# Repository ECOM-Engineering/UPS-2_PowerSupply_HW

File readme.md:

# UPS-2 Power Supply Hardware

***This read me is currently under development***  

This project is the hardware part of the superior **UPS-2** project  
https://github.com/ECOM-Engineering/UPS-2_Uninteruptible-Power-Supply.git .

If you are looking for a simple power-down switch, please refer to the  **s_shut** project  
https://github.com/ECOM-Engineering/Raspberry-Shutdown.git .

## Hardware description

### Summary

**Please refer to the [UPS-2 schematic](./doc/UPS-2 Schematic.pdf).**

UPS-2 hardware builds an uniterruptible, efficient  power supply with a wide input range. There are no glitches during switching and very low power dissipation resulting in cool operation.

Switching between main supply and backup source (usually a battery) is performed by the dedicated [TPS2121](https://www.ti.com/product/TPS2121) switch by TI with no CPU intervention. This guaranties a seamless switchover between the two power inputs. Furthermore, this design allows high efficiency thanks to the very low 56mΩ on resistance. 

5V output voltage regulation is performed by the TI [TPS56339](https://www.ti.com/product/TPS56339) 3A buck converter with an efficieny of >94%. 

Output is protected by the Raspberry standard 'ideal diode' against back driving, if Rasbperry Pi is powered through it's USB connector.

### Input Selector and Power Supply

Please refer to the [TPS2121 data sheet](https://www.ti.com/lit/ds/symlink/tps2121.pdf?ts=1623582270012&ref_url=https%253A%252F%252Fwww.google.com%252F) 

TPS2121 (U2) Power Mux is operated in th 'fast switchover' mode: If input PR1 (derived from Main input) falls below approx. 8V,  U2 switches over to the Battery input without CPU intervention. Capacitors C5, C6, C7 remove switching spikes and Voltage drop during switching over. C7 is a low EMC type with enough capacity in order to limit voltage drop during switching at up to 3A output load.

Voltage scaler allows measuring supply voltages by the ADC of the CPU. In order to minimize quiet current of the voltage sources, it uses as high resistors as possible regarding the input bias of the ADC.

### System Controller

System Controller provides 

- communication with the user via LED indicators and a switch for manual controlling 
- communication with the Raspberry CPU via serial or parallel interface
- firmware flash update via debug port or via Raspberry serial interface

UPS-2 uses an Cortex M0+ CPU of the [STM32G030](https://www.st.com/en/microcontrollers-microprocessors/stm32g030j6.html)  from STMicroelectronics. This CPU provides an incredible 32Bit performance/price ratio. 

### Debug Connector

Debug connetor J6 uses the SWD serial wire debug and flash programming. Pins 1..4 are compatible with the STM32 eval and diccovery boards.

### Hat EEPROM

This memory meets the [Raspberry-Pi Hat specification](https://github.com/raspberrypi/hats) and can be programmed by the user. **Currently, this EEPROM is not used and is unprogrammed.**

### Mode selection

For Jumper Settings and functions please refer to the [UPS-2_User Guide](../UPS-2-Project-repository/UPS-2_Uninteruptible-Power-Supply/doc/user-guide.md)

###  PCB

Board outline corresponds to the mechanical Raspberry-Pi Hat specification.   
UPS-2 uses a 1.6mm 2-layer PCB.

## Used Tools

- [KiCad](https://kicad.org/) EDA system for schematic an PCB layout.
- [Typora](https://typora.io/) for markdown texts (this readme)
- [Libre Office](https://www.libreoffice.org/) for Text and illustrations
- [git](https://git-scm.com/) and [github](https://github.com/)

## Production

This project contains all documents necessary for production including BOM with digikey part numbers and Gerber files for PCB 2-layer production.

In order to make production as simple as possible, PCB uses mostly SMD components that may be produced and soldered by nearly any prototyping service (no fine pitch, 0805 resistors, capacitors). First prototypes have been produced in Switzerland by https://www.quick-pick.ch/. 

## License

**Hardware is licensed under the open source license**  [**CERN-OHLW v2**](https://github.com/ECOM-Engineering/UPS-2_PowerSupply_HW/blob/main/doc/cern_ohl_w_v2.pdf) .

Document Copyright (c) 2021 Klaus Mezger, open source under MIT license.

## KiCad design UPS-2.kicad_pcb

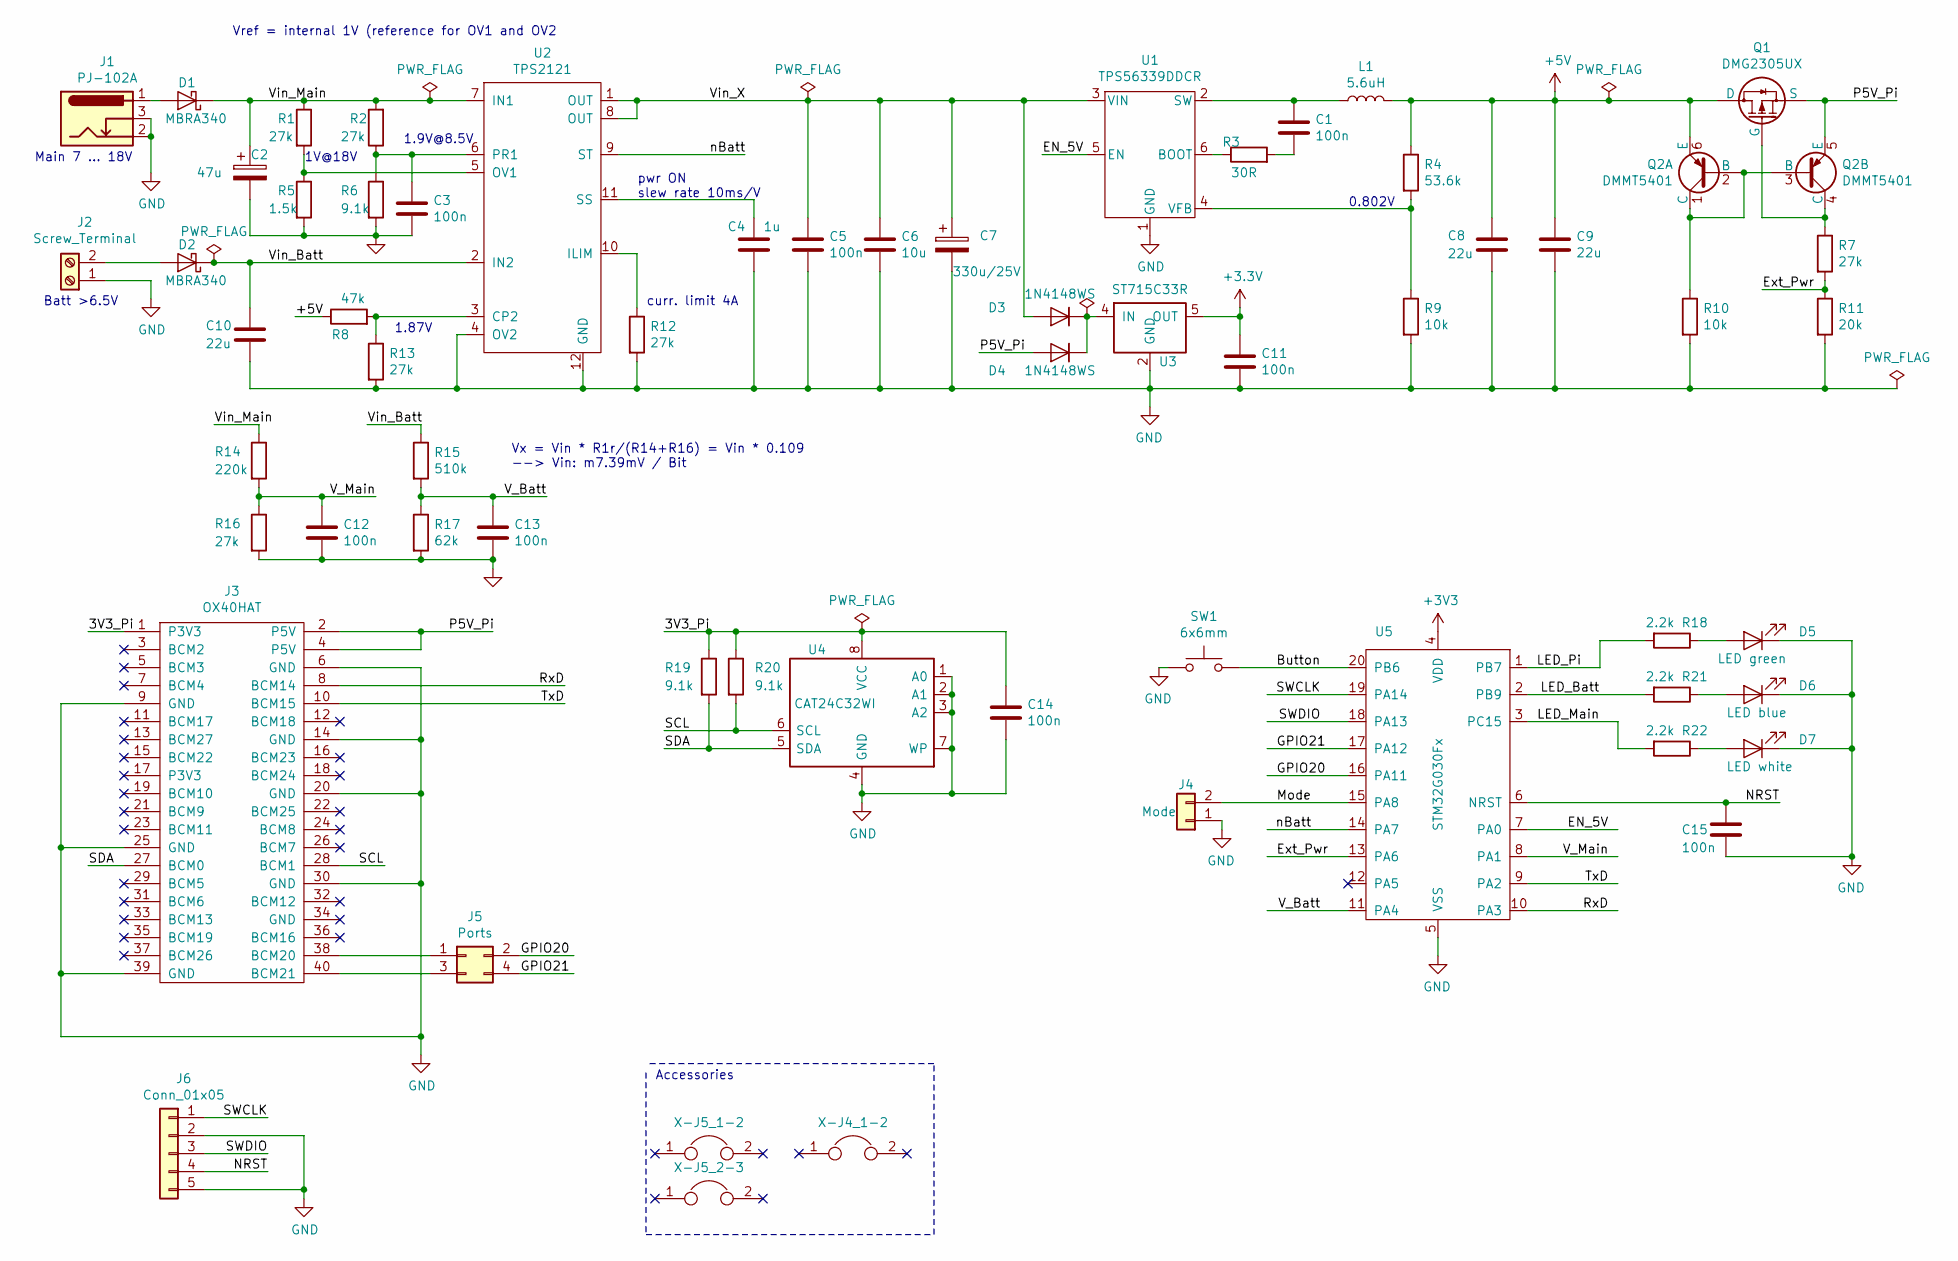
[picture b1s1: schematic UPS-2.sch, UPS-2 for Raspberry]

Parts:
C1, C3, C11, C12, C13, C14, C15: 100n; C_0805_2012Metric
C2: 47u; CP_Elec_6.3x5.3; Digi-Key_PN PCE3908CT-ND
C4: 1u; C_0805_2012Metric; Digi-Key_PN 399-7410-1-ND
C5: 100n; C_0805_2012Metric; Digi-Key_PN 399-1169-1-ND
C6: 10u; C_0805_2012Metric; Digi-Key_PN 445-9015-1-ND
C7: 330u/25V; CP_Elec_8x11.9; Digi-Key_PN PCE3906CT-ND
C8, C9: 22u; C_0805_2012Metric; Digi-Key_PN 445-14560-1-ND
C10: 22u; C_0805_2012Metric
D1, D2: MBRA340; D_SMA; Digi-Key_PN MBRA340T3GOSCT-ND
D3, D4: 1N4148WS; D_SOD-323; Digi-Key_PN 1N4148WSTR
D5: LED green; LED_1206_3216Metric; Digi-Key_PN 1516-1073-1-ND
D6: LED blue; LED_1206_3216Metric; Digi-Key_PN 1516-1072-1-ND
D7: LED white; LED_1206_3216Metric; Digi-Key_PN 1516-1074-1-ND
J1: PJ-102A; BarrelJack_CUI_PJ-102AH_Horizontal; Digi-Key_PN CP-102A-ND
J2: Screw_Terminal; TerminalBlock_bornier-2_P5.08mm; Digi-Key_PN ED2609-ND
J3: OX40HAT; PinSocket_2x20_P2.54mm_Vertical; Digi-Key_PN 612-HLE-120-02-F-DV-BE-ND
J4: Mode; PinHeader_1x02_P2.54mm_Vertical
J5: Ports; PinHeader_2x02_P2.54mm_Vertical
J6: Conn_01x05; PinHeader_1x05_P2.54mm_Vertical
L1: 5.6uH; L_Bourns_SRR1260; Digi-Key_PN SRR1260A-5R6YCT-ND
Q1: DMG2305UX; SOT-23; Digi-Key_PN DMG2305UX-13DICT-ND
Q2: DMMT5401; SOT-23-6; Digi-Key_PN DMMT5401-FDICT-ND
R1, R2, R7, R12, R13, R16: 27k; R_0805_2012Metric
R3: 30R; R_0805_2012Metric
R4: 53.6k; R_0805_2012Metric
R5: 1.5k; R_0805_2012Metric
R6, R19, R20: 9.1k; R_0805_2012Metric
R8: 47k; R_0805_2012Metric
R9, R10: 10k; R_0805_2012Metric
R11: 20k; R_0805_2012Metric
R14: 220k; R_0805_2012Metric
R15: 510k; R_0805_2012Metric
R17: 62k; R_0805_2012Metric
R18, R21, R22: 2.2k; R_0805_2012Metric
SW1: 6x6mm; SW_SPST_PTS645; Digi-Key_PN CKN9087DKR-ND
U1: TPS56339DDCR; SOT-23-6; Digi-Key_PN 296-53568-1-ND
U2: TPS2121; TPS2121RUXR_V2; Digi-Key_PN 296-53410-1-ND
U3: ST715C33R; SOT-353_SC-70-5; Digi-Key_PN 497-15509-1-ND
U4: CAT24C32WI; SO-8_3.9x4.9mm_P1.27mm; Digi-Key_PN CAT24C32WI-GT3CT-ND
U5: STM32G030Fx; TSSOP-20_4.4x6.5mm_P0.65mm; Digi-Key_PN STM32G030F6P6
X-J4_1-2, X-J5_1-2, X-J5_2-3: Jumper 2.54; Digi-Key_PN S9337-ND

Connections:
+5V: C8.1, C9.1, L1.2, Q1.3 (D), Q2.6 (E), R4.1, R8.1
/3V3_Pi: C14.1, J3.1 (P3V3), R19.1, R20.1, U4.8 (VCC)
/Button: SW1.1, U5.20 (PB6)
/EN_5V: U1.5 (EN), U5.7 (PA0)
/Ext_Pwr: R7.2, R11.1, U5.13 (PA6)
/GPIO20: J5.2, U5.16 (PA11)
/GPIO21: J5.4, U5.17 (PA12)
/LED_Batt: R21.2, U5.2 (PB9)
/LED_Main: R22.2, U5.3 (PC15)
/LED_Pi: R18.2, U5.1 (PB7)
/Mode: J4.2, U5.15 (PA8)
/NRST: C15.1, J6.4, U5.6 (NRST)
/P5V_Pi: D4.2 (A), J3.2 (P5V), J3.4 (P5V), Q1.2 (S), Q2.5 (E)
/RxD: J3.8 (BCM14), U5.10 (PA3)
/SCL: J3.28 (BCM1), R20.2, U4.6 (SCL)
/SDA: J3.27 (BCM0), R19.2, U4.5 (SDA)
/SWCLK: J6.1, U5.19 (PA14)
/SWDIO: J6.3, U5.18 (PA13)
/TxD: J3.10 (BCM15), U5.9 (PA2)
/V_Batt: C13.1, R15.2, R17.1, U5.11 (PA4)
/V_Main: C12.1, R14.2, R16.1, U5.8 (PA1)
/Vin_Batt: C10.1, D2.1 (K), R15.1, U2.2 (IN2)
/Vin_Main: C2.1, D1.1 (K), R1.1, R2.2, R14.1, U2.7 (IN1)
/Vin_X: C5.1, C6.1, C7.1, D3.2 (A), U1.3 (VIN), U2.1 (OUT), U2.8 (OUT)
/nBatt: U2.9 (ST), U5.14 (PA7)
GND: C2.2, C3.2, C4.2, C5.2, C6.2, C7.2, C8.2, C9.2, C10.2, C11.2, C12.2, C13.2, C14.2, C15.2, D5.1 (K), D6.1 (K), D7.1 (K), J1.2, J1.3, J2.1, J3.6 (GND), J3.9 (GND), J3.14 (GND), J3.20 (GND), J3.25 (GND), J3.30 (GND), J3.39 (GND), J4.1, J6.2, J6.5, R5.2, R6.2, R9.2, R10.2, R11.2, R12.2, R13.2, R16.2, R17.2, SW1.2, U1.1 (GND), U2.4 (OV2), U2.12 (GND), U3.2 (GND), U4.1 (A0), U4.2 (A1), U4.3 (A2), U4.4 (GND), U4.7 (WP), U5.5 (VSS)
unnamed: C1.1, L1.1, U1.2 (SW)
unnamed: C1.2, R3.2
unnamed: C3.1, R2.1, R6.1, U2.6 (PR1)
unnamed: C4.1, U2.11 (SS)
unnamed: D1.2 (A), J1.1
unnamed: D2.2 (A), J2.2
unnamed: D3.1 (K), D4.1 (K), U3.4 (IN)
unnamed: D5.2 (A), R18.1
unnamed: D6.2 (A), R21.1
unnamed: D7.2 (A), R22.1
unnamed: J3.38 (BCM20), J5.1
unnamed: J3.40 (BCM21), J5.3
unnamed: Q1.1 (G), Q2.4 (C), R7.1
unnamed: Q2.1 (C), Q2.2 (B), Q2.3 (B), R10.1
unnamed: R1.2, R5.1, U2.5 (OV1)
unnamed: R3.1, U1.6 (BOOT)
unnamed: R4.2, R9.1, U1.4 (VFB)
unnamed: R12.1, U2.10 (ILIM)
unnamed: R8.2, R13.1, U2.3 (CP2)

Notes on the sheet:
pwr ON slew rate 10ms/V
curr. limit 4A
1.87V
1.9V@8.5V
1V@18V
Vref = internal 1V (reference for OV1 and OV2
0.802V
Accessories
Vx = Vin * R1r/(R14+R16) = Vin * 0.109 --> Vin: m7.39mV / Bit
Batt >6.5V
Main 7 ... 18V

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
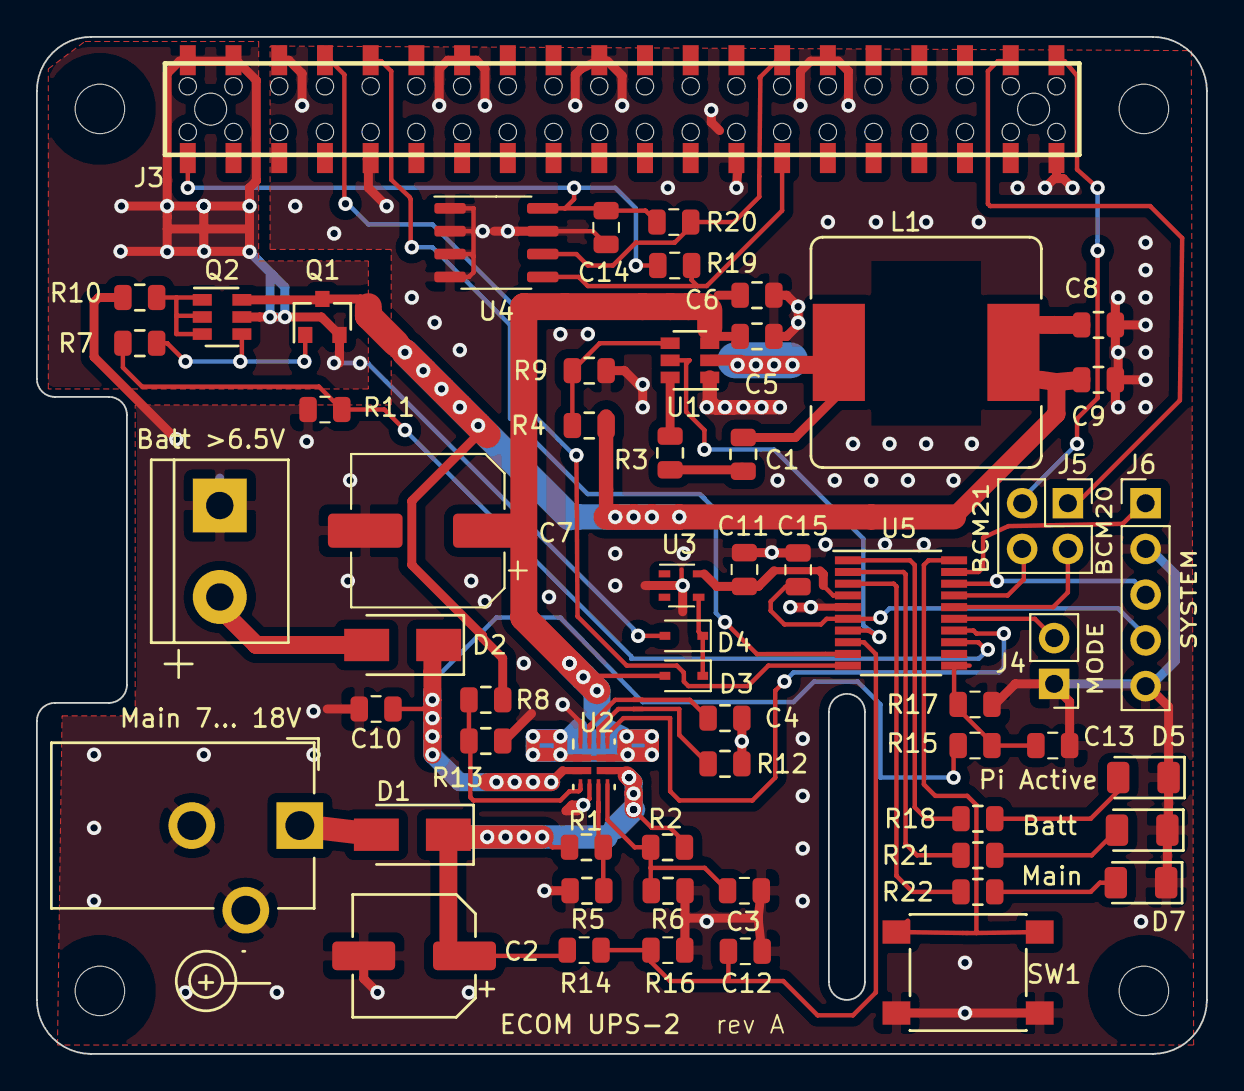
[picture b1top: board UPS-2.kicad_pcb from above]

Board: 2 copper layers, 65.0 x 56.5 mm, 59 parts (0 on the bottom side), 46 nets.

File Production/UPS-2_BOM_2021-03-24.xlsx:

| UPS-2_BOM_2021-03-23 |  |  |  | ECOM ENGINEERING
ID | Reference | Quantity | Value | Footprint | Digi-Key_PN
1 | C2 | 1 | 47u | Capacitor_SMD:CP_Elec_6.3x5.3 | PCE3908CT-ND
2 | C4 | 1 | 1u | Capacitor_SMD:C_0805_2012Metric | 399-7410-1-ND
3 | C5 C1 C13 C12 C15 C11 C3 C14 | 8 | 100n | Capacitor_SMD:C_0805_2012Metric | 399-1169-1-ND
4 | C6 | 1 | 10u | Capacitor_SMD:C_0805_2012Metric | 445-9015-1-ND
5 | C7 | 1 | 330u/25V | Capacitor_SMD:CP_Elec_8x11.9 | PCE3906CT-ND
6 | C9 C8 C10 | 3 | 22u | Capacitor_SMD:C_0805_2012Metric | 445-14560-1-ND
7 | D2 D1 | 2 | MBRA340 | Diode_SMD:D_SMA | MBRA340T3GOSCT-ND
8 | D4 D3 | 2 | 1N4148WS | Diode_SMD:D_SOD-323 | 1N4148WSTR
9 | D5 | 1 | LED green | LED_SMD:LED_1206_3216Metric | 1516-1073-1-ND
10 | D6 | 1 | LED blue | LED_SMD:LED_1206_3216Metric | 1516-1072-1-ND
11 | D7 | 1 | LED white | LED_SMD:LED_1206_3216Metric | 1516-1074-1-ND
12 | J1 | 1 | PJ-102A | Connector_BarrelJack:BarrelJack_CUI_PJ-102AH_Horizontal | CP-102A-ND
13 | J2 | 1 | Screw_Terminal | TerminalBlock:TerminalBlock_bornier-2_P5.08mm | ED2609-ND
14 | J3 | 1 | OX40HAT | Connector_PinSocket_2.54mm:PinSocket_2x20_P2.54mm_Vertical | 612-HLE-120-02-F-DV-BE-ND
15 | J4 | 1 | Mode | Connector_PinHeader_2.54mm:PinHeader_1x02_P2.54mm_Vertical
16 | J5 | 1 | Ports | Connector_PinHeader_2.54mm:PinHeader_2x02_P2.54mm_Vertical
17 | J6 | 1 | Conn_01x05 | Connector_PinHeader_2.54mm:PinHeader_1x05_P2.54mm_Vertical
18 | L1 | 1 | 5.6uH | Inductor_SMD:L_Bourns_SRR1260 | SRR1260A-5R6YCT-ND
19 | Q1 | 1 | DMG2305UX | Package_TO_SOT_SMD:SOT-23 | DMG2305UX-13DICT-ND
20 | Q2 | 1 | DMMT5401 | Package_TO_SOT_SMD:SOT-23-6 | DMMT5401-FDICT-ND
21 | R11 | 1 | 20k | Resistor_SMD:R_0805_2012Metric
22 | R12 R2 R1 R7 R13 R16 | 6 | 27k | Resistor_SMD:R_0805_2012Metric
23 | R14 | 1 | 220k | Resistor_SMD:R_0805_2012Metric
24 | R15 | 1 | 510k | Resistor_SMD:R_0805_2012Metric
25 | R17 | 1 | 62k | Resistor_SMD:R_0805_2012Metric
26 | R22 R18 R21 | 3 | 2.2k | Resistor_SMD:R_0805_2012Metric
27 | R3 | 1 | 30R | Resistor_SMD:R_0805_2012Metric
28 | R4 | 1 | 53.6k | Resistor_SMD:R_0805_2012Metric
29 | R5 | 1 | 1.5k | Resistor_SMD:R_0805_2012Metric
30 | R6 R20 R19 | 3 | 9.1k | Resistor_SMD:R_0805_2012Metric
31 | R8 | 1 | 47k | Resistor_SMD:R_0805_2012Metric
32 | R9 R10 | 2 | 10k | Resistor_SMD:R_0805_2012Metric
33 | SW1 | 1 | 6x6mm | Button_Switch_SMD:SW_SPST_PTS645 | CKN9087DKR-ND
34 | U1 | 1 | TPS56339DDCR | Package_TO_SOT_SMD:SOT-23-6 | 296-53568-1-ND
35 | U2 | 1 | TPS2121 | project_footprints:TPS2121RUXR_V2 | 296-53410-1-ND
36 | U3 | 1 | ST715C33R | Package_TO_SOT_SMD:SOT-353_SC-70-5 | 497-15509-1-ND
37 | U4 | 1 | CAT24C32WI | Package_SO:SO-8_3.9x4.9mm_P1.27mm | CAT24C32WI-GT3CT-ND
38 | U5 | 1 | STM32G030Fx | Package_SO:TSSOP-20_4.4x6.5mm_P0.65mm | STM32G030F6P6
39 | X-J5_1-2 X-J5_2-3 X-J4_1-2 | 3 | Jumper 2.54 |  | S9337-ND
 | Off board:
40 | J3 + |  | Header 2x40 | 40 pin Stacking Header | 1528-1783-ND
40a | J3 + alternative |  |  | Adafruit 2x20 Extra tall header ID 1979 | xxx

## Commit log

2021-03-26 removed internal directories
2021-03-26 removed directory Korrespondenz
2021-03-26 removed internal files
2021-03-26 File VoltageDevider removed
2021-03-27 url removed
2021-03-27 url links removed
2021-03-27 License and cern doc added
2021-03-29 readme + schematic update
2021-03-29 readme and schematic PDF added
2021-07-26 pictures added
2021-07-26 path to pics corrected
2021-07-26 test png image
2021-07-26 images removed

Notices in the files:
UPS-2.sch:
Copyright(c) 2020 Klaus Mezger
Licensed under CERN-OHLW v2
